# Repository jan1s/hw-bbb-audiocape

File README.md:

hw-bbb-audiocape
================

First of all: This project is a clone of [CircuitCo Audio Cape][circuitco].

It is not commercial in any form, just fun for me to play around.
If you want an Audio Cape, go and get one of theirs.

## Hardware

Project schematic.

Render of the board.

## Setup on Arch

The setup guide is mainly taken from [eLinux.org - BBB Audio Cape RevB Getting Started][gettingstarted].

Get the tools if not already installed:

`pacman -S wget`

`pacman -S unzip`

`pacman -S dct-overlay`

Download and unzip the device tree source:

`wget http://elinux.org/images/1/10/BB-BONE-AUDI-02-00A0.zip`

`unzip BB-BONE-AUDI-02-00A0.zip`

Compile the device tree file and move it to /lib/firmware:

`dtc -O dtb -o BB-BONE-AUDI-02-00A0.dtbo -b 0 -@ BB-BONE-AUDI-02-00A0.dts`

`mv BB-BONE-AUDI-02-00A0.dtbo /lib/firmware`

Notice that the dtc-overlay version needs to be installed, since the old dtc is not accepting the @ option.

The Cape is sharing the audio signal with the onboard HDMI. Therefore HDMI audio needs to be disabled.
Edit the uEnv.txt file, that your uboot is using:

`optargs=capemgr.disable_partno=BB-BONELT-HDMI`

In order to activate the cape you need to reboot.
Load the Device Tree file for the cape:

`echo BB-BONE-AUDI-02 > /sys/devices/bone_capemgr*/slots`

To make that persistent just add the following line in /etc/default/capemgr :

`CAPE=BB-BONE-AUDI-02`

## Test and play

Play alternating noise on the 2 output channels:

`speaker-test -c 2`

Play alternating sine waves on the 2 output channels:

`speaker-test -c 2 -t sine`

## BOM
| Identifier | Type/Value | Quantity | Comment | Supplier Id | Supplier |
| ---        | ---        | ---      | ---     | ---         | ---      |
| R1, R2 | 0 Ω | 2 | not populated | SMD-0603 0  | [Reichelt][reichelt] |
| R5, R6 | 33 Ω | 2 |  | SMD-0603 33 | [Reichelt][reichelt] |
| C3, C4, C20, C21 | 47 pF | 2 |  | NPO-G0603 47P | [Reichelt][reichelt] |
| C13 | 10 nF | 1 |  | X7R-G0603 10N | [Reichelt][reichelt] |
| C1, C2, C5, C6, C15, C16 | 100 nF | 6 |  | X7R-G0603 100N | [Reichelt][reichelt] |
| C7-C10, C14, C17 | 10 µF | 6 |  | X5R-G0603 10/6 | [Reichelt][reichelt] |
| C18, C19 | 47 µF | 2 |  | X5R-G1206 47/6 | [Reichelt][reichelt] |
| J1, J2 | 4pol TRS Jack | 2 |  | LUM 1503-13V | [Reichelt][reichelt] |
| J3, J4 | 2row Pin Header | 2 |  | SL 2X25G 2,54 | [Reichelt][reichelt] |
| D1-D4 | Suppressor Diodes | 4 |  | 863-ESD9B3.3ST5G | [Mouser][mouser] |
| U1 | Stereo CODEC | 1 |  | 595-TLV320C3104IRHBT | [Mouser][mouser] |
| U2 | LDO 1.8V | 1 |  | 595-TLV70218DBVR | [Mouser][mouser] |

[reichelt]: http://www.reichelt.de
[mouser]: http://mouser.com

[itead-pcb]: http://imall.iteadstudio.com/open-pcb/pcb-prototyping.html

[circuitco]: http://elinux.org/CircuitCo:Audio_Cape_RevB
[gettingstarted]: http://elinux.org/BBB_Audio_Cape_RevB_Getting_Started

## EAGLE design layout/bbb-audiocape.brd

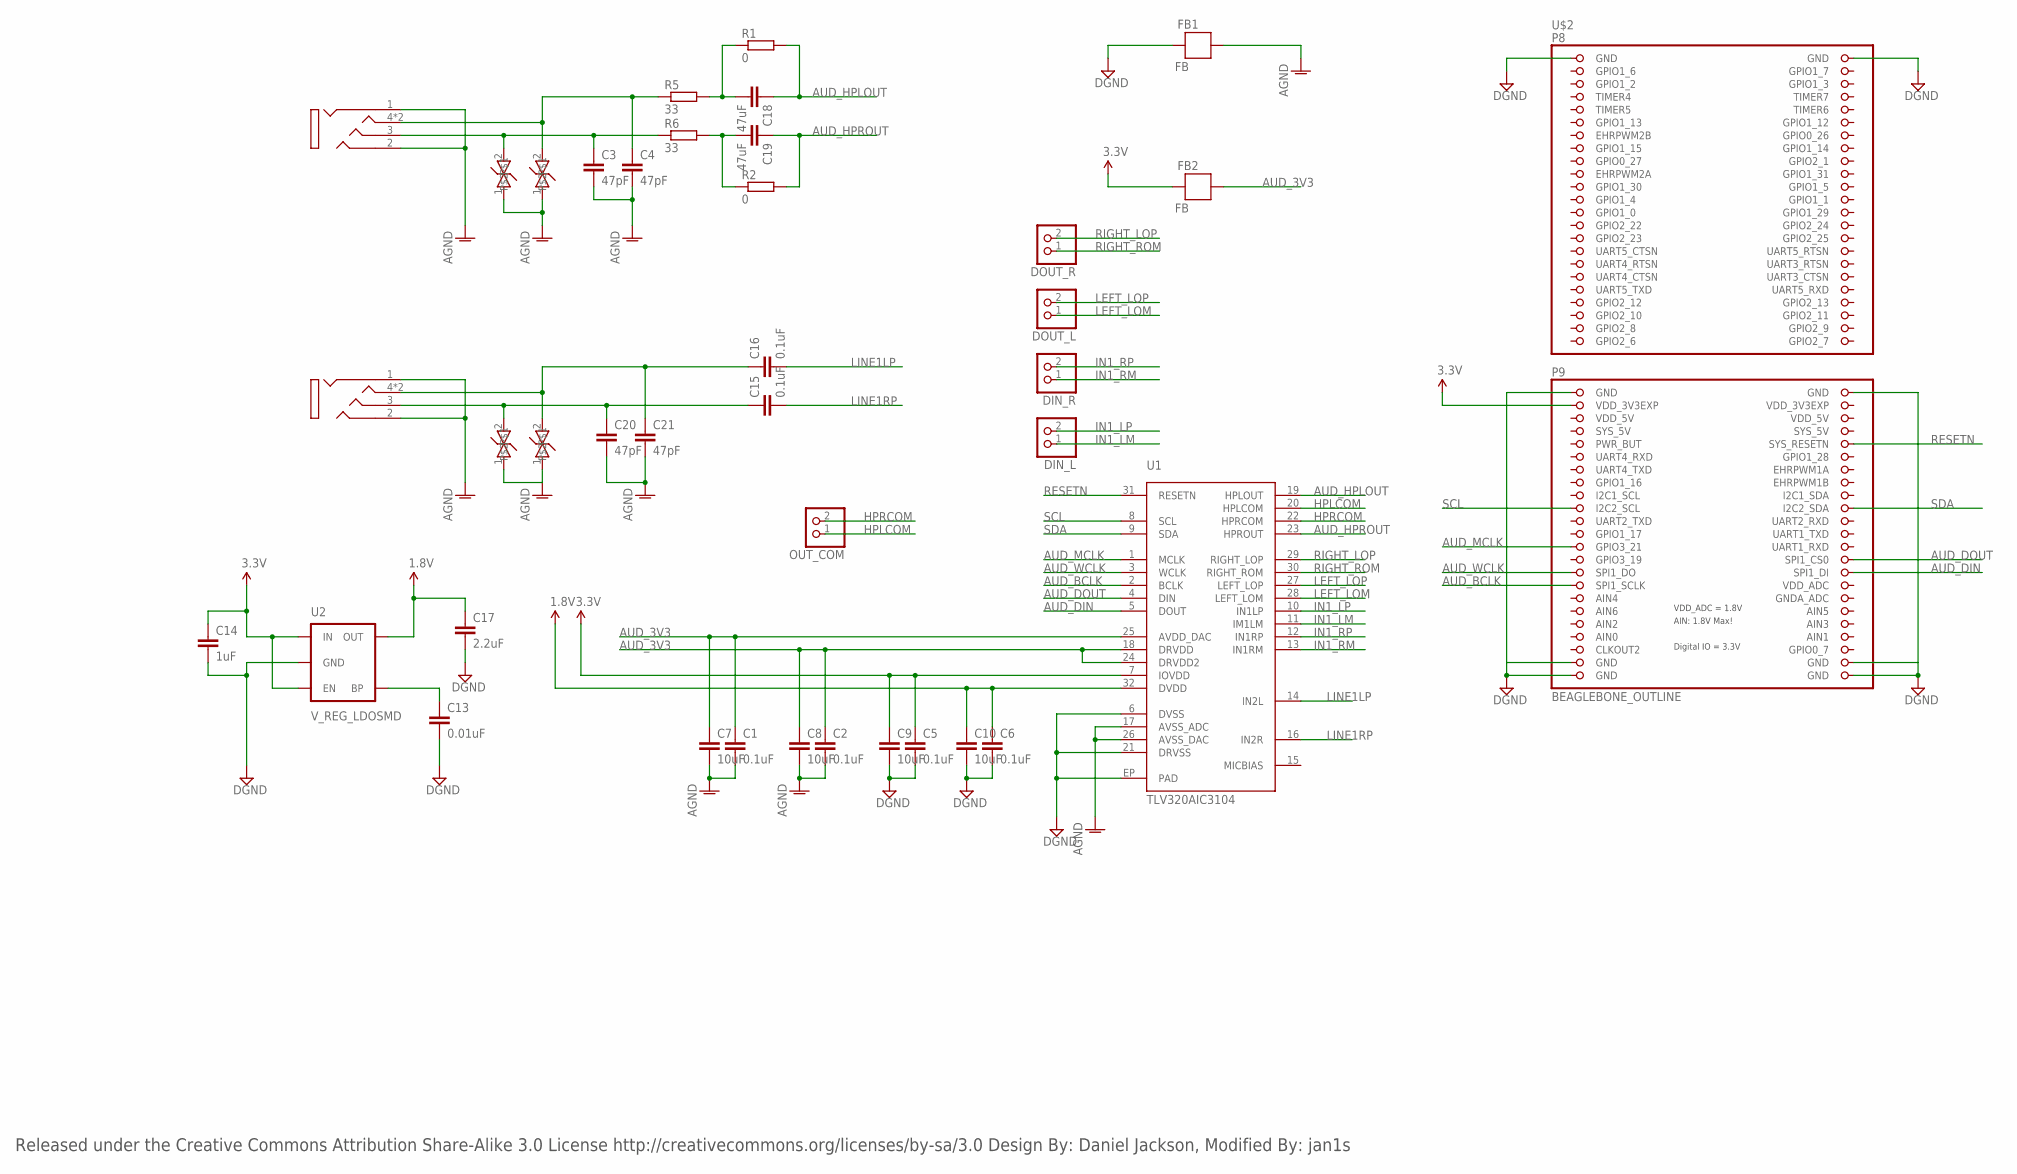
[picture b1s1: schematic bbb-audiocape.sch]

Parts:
C1, C2, C5, C6, C15, C16: 0.1uF; C0603
C3, C4, C20, C21: 47pF; C0603
C7, C8, C9, C10: 10uF; C0603
C13: 0.01uF; C0603
C14: 1uF; C0603
C17: 2.2uF; C0603
C18, C19: 47uF; C1206
D1, D2, D3, D4: PGB0010603MR; 0603
DIN_L: HEADER-1X2ROUND; 1X02_ROUND
DIN_R: HEADER-1X2ROUND; 1X02_ROUND
DOUT_L: HEADER-1X2ROUND; 1X02_ROUND
DOUT_R: HEADER-1X2ROUND; 1X02_ROUND
FB1, FB2: FB; 0603
OUT_COM: HEADER-1X2ROUND; 1X02_ROUND
R1, R2: 0; R0603
R5, R6: 33; R0603
U1: TLV320AIC3104; QFN-32
U2: V_REG_LDOSMD; SOT23-5
U$2: BEAGLEBONE_OUTLINE; BEAGLEBONE_SHIELD
U$3, U$5: 1503_13; 1503-03

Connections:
1.8V: C6.1, C10.1, C17.1, U1.32 (DVDD), U2.5 (OUT)
3.3V: C5.1, C9.1, C14.1, FB2.2, U1.7 (IOVDD), U2.1 (IN), U2.3 (EN), U$2.49 (VDD_3V3EXP)
AGND: C1.2, C2.2, C3.2, C4.2, C7.2, C8.2, C20.2, C21.2, D1.1, D2.1, D3.1, D4.1, FB1.1, U1.17 (AVSS_ADC), U1.26 (AVSS_DAC), U$3.1, U$3.2, U$5.1, U$5.2
AUD_3V3: C1.1, C2.1, C7.1, C8.1, FB2.1, U1.18 (DRVDD), U1.24 (DRVDD2), U1.25 (AVDD_DAC)
AUD_BCLK: U1.2 (BCLK), U$2.77 (SPI1_SCLK)
AUD_DIN: U1.5 (DOUT), U$2.76 (SPI1_DI)
AUD_DOUT: U1.4 (DIN), U$2.74 (SPI1_CS0)
AUD_HPLOUT: C18.1, R1.2, U1.19 (HPLOUT)
AUD_HPROUT: C19.1, R2.2, U1.23 (HPROUT)
AUD_MCLK: U1.1 (MCLK), U$2.71 (GPIO3_21)
AUD_WCLK: U1.3 (WCLK), U$2.75 (SPI1_DO)
DGND: C5.2, C6.2, C9.2, C10.2, C13.2, C14.2, C17.2, FB1.2, U1.6 (DVSS), U1.21 (DRVSS), U1.EP (PAD), U2.2 (GND), U$2.1 (GND), U$2.2 (GND), U$2.47 (GND), U$2.48 (GND), U$2.89 (GND), U$2.90 (GND), U$2.91 (GND), U$2.92 (GND)
GNDA_ADC: U$2.80 (GNDA_ADC)
HPLCOM: OUT_COM.1, U1.20 (HPLCOM)
HPRCOM: OUT_COM.2, U1.22 (HPRCOM)
IN1_LM: DIN_L.1, U1.11 (IM1LM)
IN1_LP: DIN_L.2, U1.10 (IN1LP)
IN1_RM: DIN_R.1, U1.13 (IN1RM)
IN1_RP: DIN_R.2, U1.12 (IN1RP)
J1: C4.1, D2.2, R5.1, U$3.4, U$3.4-2 (4)
LEFT_LOM: DOUT_L.1, U1.28 (LEFT_LOM)
LEFT_LOP: DOUT_L.2, U1.27 (LEFT_LOP)
LINE1LP: C16.2, U1.14 (IN2L)
LINE1RP: C15.2, U1.16 (IN2R)
unnamed: C15.1, C20.1, D3.2, U$5.3
unnamed: C18.2, R1.1, R5.2
unnamed: C19.2, R2.1, R6.2
unnamed: C3.1, D1.2, R6.1, U$3.3
unnamed: C16.1, C21.1, D4.2, U$5.4, U$5.4-2 (4)
unnamed: C13.1, U2.4 (BP)
RESETN: U1.31 (RESETN), U$2.56 (SYS_RESETN)
RIGHT_LOP: DOUT_R.2, U1.29 (RIGHT_LOP)
RIGHT_ROM: DOUT_R.1, U1.30 (RIGHT_ROM)
SCL: U1.8 (SCL), U$2.65 (I2C2_SCL)
SDA: U1.9 (SDA), U$2.66 (I2C2_SDA)
SYS_5V: U$2.53 (SYS_5V), U$2.54 (SYS_5V)
VDD_3V3EXP: U$2.50 (VDD_3V3EXP)
VDD_5V: U$2.51 (VDD_5V), U$2.52 (VDD_5V)
VDD_ADC: U$2.78 (VDD_ADC)

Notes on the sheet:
Released under the Creative Commons Attribution Share-Alike 3.0 License http://creativecommons.org/licenses/by-sa/3.0 Design By: Daniel Jackson, Modified By: jan1s

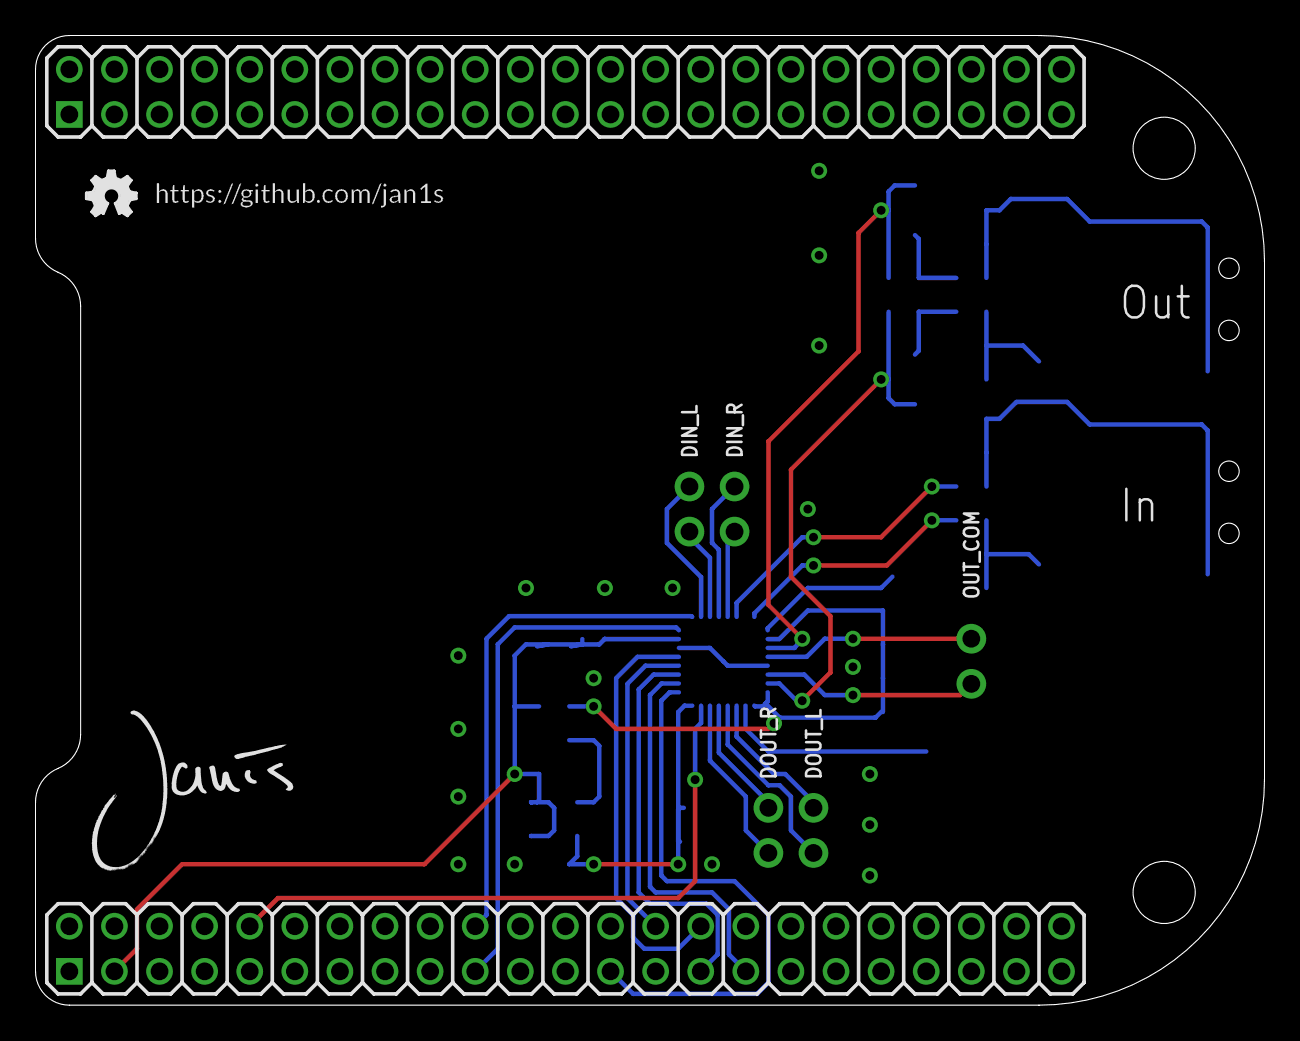
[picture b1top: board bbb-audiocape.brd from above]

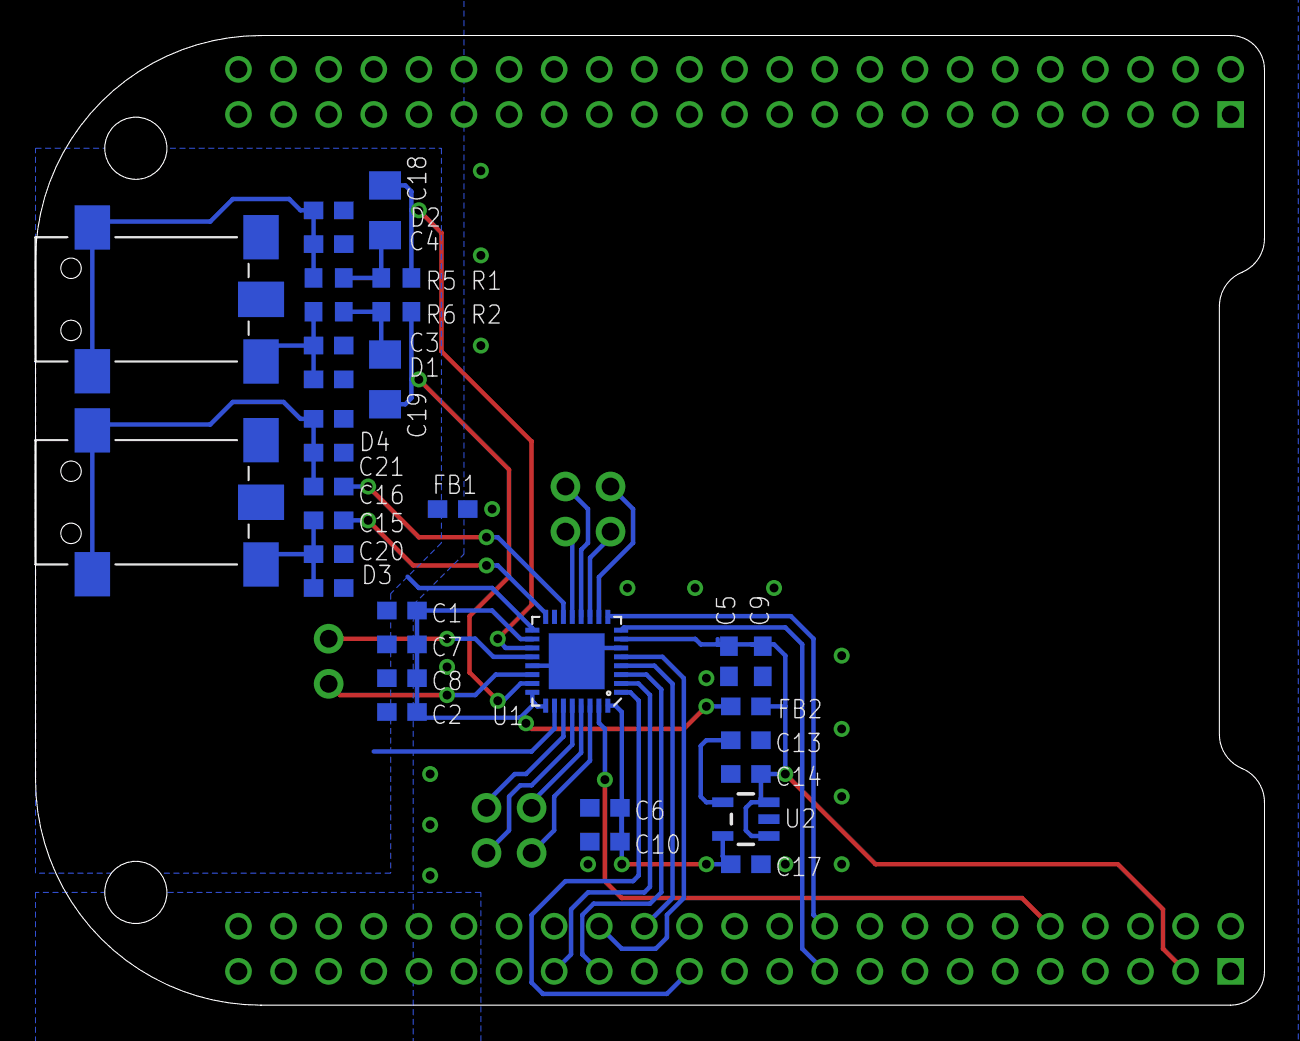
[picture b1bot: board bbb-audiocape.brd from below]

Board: 2 copper layers, 69.2 x 54.6 mm, 42 parts (33 on the bottom side), 36 nets.

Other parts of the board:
U$1: GITHUB/JAN1S
U$4: JANIS_10MM
U$6: OSHW_FILLX100_NOTEXT

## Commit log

2014-03-18 Finished Silkscreen
2014-04-11 Added some vias
2014-04-11 Updated BOM
2014-04-11 Completed BOM
2014-04-11 Finished production files
2014-09-04 Added docu pic, Added License stuff
2014-09-04 Changed README
2014-09-04 Fixed very minor typo

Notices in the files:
parts and their libraries:
SparkFun-Passives: Licensing: CC v3.0 Share-Alike You are welcome to use this library for commercial purposes.
microbuilder: This work is placed in the public domain, and may be freely used for commercial and non-commercial work with the following conditions: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
